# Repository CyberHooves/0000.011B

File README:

HAOS REDRO PN: 0000 0001
========================

This is a single sided PCB for battery construction. Multiple boards can be stacked using M3 threaded spacers or M3 studding and plain spacers. Each board provides additional M3 screw holes for positive and negative connections, either to cables with ring terminals or to adjacent boards via conductive spacers. A pin header is provided for cell stack monitoring and cell balancing connections. Note that this design is unsuitable for high-current applications and the maximum continuous current should be limited to 2A per cell.

Cell information for a fully-populated single board:
----------------------------------------------------
Type:		18650
Count:		8
Configuration:  4P2S

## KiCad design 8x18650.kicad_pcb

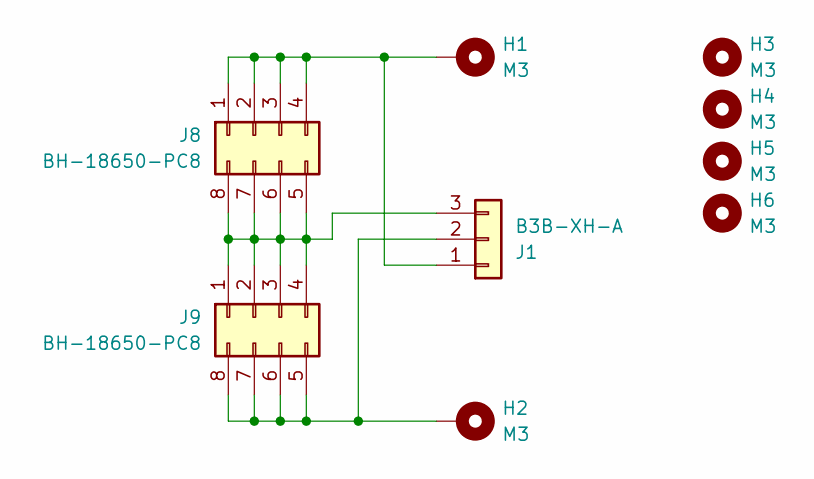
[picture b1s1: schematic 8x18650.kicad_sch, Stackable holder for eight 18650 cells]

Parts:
H1, H2: M3; MountingHole_3.2mm_M3_Pad
H3, H4, H5, H6: M3; MountingHole_3.2mm_M3
J1: B3B-XH-A; JST_XH_B3B-XH-AM_1x03_P2.50mm_Vertical
J8, J9: BH-18650-PC8; BH-81650-PC8

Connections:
unnamed: H1.1, J1.1, J8.1, J8.2, J8.3, J8.4
unnamed: H2.1, J1.2, J9.5, J9.6, J9.7, J9.8
unnamed: J1.3, J8.5, J8.6, J8.7, J8.8, J9.1, J9.2, J9.3, J9.4

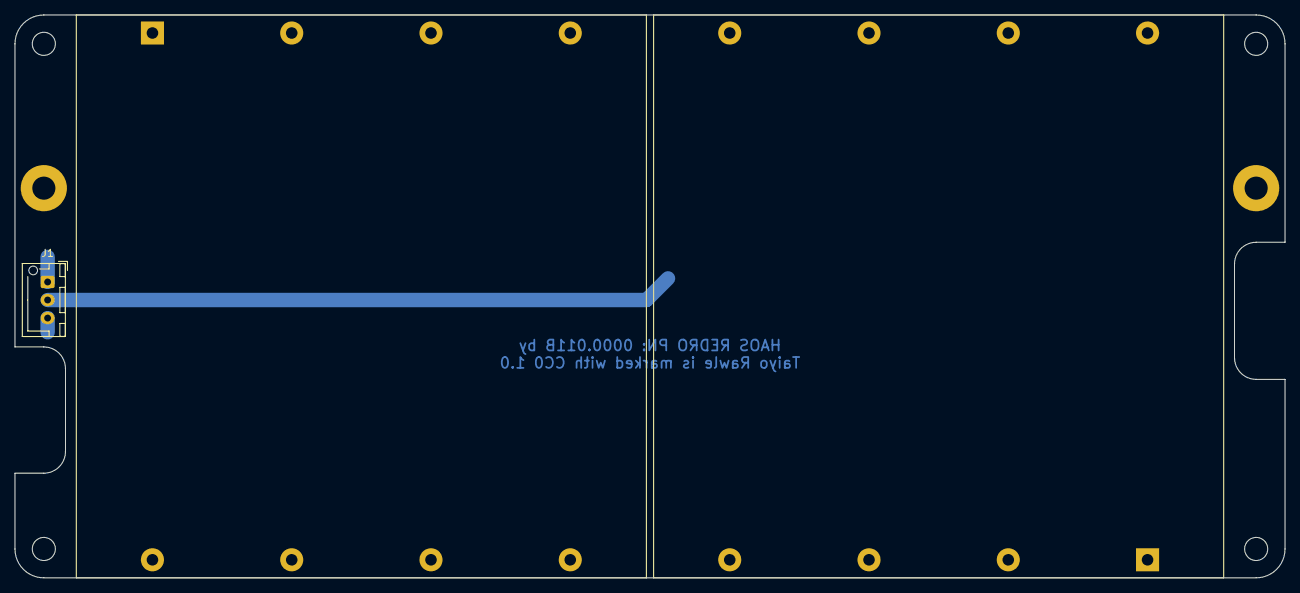
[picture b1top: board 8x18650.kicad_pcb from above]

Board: 2 copper layers, 176.0 x 78.0 mm, 9 parts (0 on the bottom side), 3 nets.

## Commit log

2025-01-25 Updated license information
2025-01-25 minor cleanups
2025-01-27 Updated license infomration.

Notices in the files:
8x18650.kicad_pcb:
HAOS REDRO PN: 0000.011B by Taiyo Rawle is marked with CC0 1.0
